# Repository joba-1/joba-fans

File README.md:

# joba-fans — quiet, networked fans for radiators

A small system that puts **PC fans on top of panel radiators** and controls them over WiFi. Its job is
to make a heat pump that cools through wall-hung radiators work properly: a low-mounted radiator hardly
emits any cooling power by free convection, so the heat pump short-cycles. Forced air over the fins
recovers a factor of roughly 3–4 (reasoning and sizing: [fan-mount/docs/requirements.md](fan-mount/docs/requirements.md)).

Four parts, each in its own directory with its own README:

| Part | What it is | Technology |
|---|---|---|
| [`fan-controller/`](fan-controller/) | The board: four PWM fan channels with tach read-back on a socketed ESP32 module | KiCad 10, Python generators |
| [`fan-housing/`](fan-housing/) | A snap-fit 3D-printed case for that board | OpenSCAD |
| [`fan-remote/`](fan-remote/) | The firmware: web remote, MQTT, Home Assistant discovery, soft start | PlatformIO / Arduino-ESP32 |
| [`fan-mount/`](fan-mount/) | 3D-printed mounts that hold 120 mm fans on the radiators | FreeCAD, STL |

## How it fits together

```mermaid
flowchart LR
  subgraph radiator["Radiator"]
    F["PC fans, 120 mm, 4-pin PWM<br/>in <b>fan-mount</b> parts"]
  end
  subgraph box["<b>fan-housing</b> (printed case)"]
    B["<b>fan-controller</b> board<br/>XIAO ESP32-C3<br/>running <b>fan-remote</b>"]
  end
  PSU["12 V supply"] --> B
  B -- "PWM 25 kHz, +12 V<br/>tach back" --> F
  B <-- "WiFi" --> N["Browser (web remote)<br/>MQTT broker + Home Assistant"]
  N -.-> HP["heat-pump / room control<br/>(outside this repo)"]
```

* A **radiator** carries up to ~9 fans in `fan-mount` parts. The fans are standard 120 × 25 mm PC fans.
* Each **controller board** drives four channels; several fans can share a channel (same speed, one tach).
  A 12 V supply feeds the board, which passes 12 V on to the fans.
* The **firmware** gives each board a web page, MQTT topics and a Home Assistant device. Speeds are set
  there — by hand, or by automation (for instance a heat-pump cooling signal in Home Assistant). The
  temperature logic is deliberately *not* part of this repo; the firmware only exposes the fans.
* The **housing** protects the board and brings the barrel jack, USB-C port and four fan cables out.

### The interfaces, and how each was checked

| Interface | Contract | Checked |
|---|---|---|
| firmware ↔ board | FAN1–4: PWM on D1/D3/D7/D6, tach on D2/D4/D10/D5 (GPIO 3/5/20/21 and 4/6/10/7) | The pin table in `fan-remote/src/Fans.cpp` equals the pad nets read out of `fan-controller.kicad_pcb`; the firmware builds for the XIAO ESP32-C3 and C6 and its 22 unit tests pass |
| board ↔ fans | 4-pin PC fan, pinout GND / +12 V / tach / PWM, 25 kHz PWM, 3.3 V logic | Pinout equals the PCB nets of J2–J5; 25 kHz is what the firmware generates. Total current of all fans must stay below the 1.5 A polyfuse |
| board ↔ housing | outer dimensions, connector positions, USB-C end, jack overhang | `fan-housing/board_params.scad` is regenerated from the PCB and is identical; `check_fit.py` passes (latch strain 1.5 %, ≥ 2.2 mm of air above every part, no tab hits a component); the STLs match the OpenSCAD source; the USB-C cut-out sits at the module's USB end (the module's pad rows run along the board's short side, with D6/D7 and the antenna at the other end) |
| fans ↔ mounts | 120 mm fan, 25 mm thick, 105 mm hole pattern | Collar inside 120.6 mm, rest height 2 mm, collar 28 mm; STL sizes match the spreadsheet dimensions (226.6 × 126.6 × 28 mm) |
| firmware ↔ Home Assistant | MQTT discovery, topics `fan-control/<id>/…` | Tested on a bench board with HA (see `fan-remote/docs/test.md`) |
| housing ↔ mounts | none (they only meet through the fans and cables) | — |

Fitting the parts together turned up four things worth knowing; all are written down in the component
READMEs:

1. The fan headers on the board are **unshrouded** — a reversed connector puts 12 V on a tach line
   ([fan-controller](fan-controller/README.md#known-issues)).
2. The PWM lines **float during an ESP reset**, so fans can burst briefly (also fan-controller; a pull-down
   is a candidate for board revision 2).
3. A radiator needs **more fans than a board has channels**, so fans must be chained per channel
   ([fan-mount](fan-mount/README.md#how-it-fits-the-rest-of-the-system)); this has not been tried yet.
4. The firmware has not yet run **on the real board** — only on a bench XIAO with one fan.

## Building it

1. **Board.** Order from the files in [`fan-controller/fab/`](fan-controller/fab/) (a PCB service that does
   assembly; revision 1 went to PCBWay), or regenerate them with `fan-controller/scripts/make_fab.sh`.
   Plug a XIAO ESP32-C3 into the sockets.
2. **Case.** Print the three STLs from [`fan-housing/stl/`](fan-housing/stl/) (PETG, no supports).
3. **Mounts.** Pick the variant for your radiator in [`fan-mount/cad/`](fan-mount/cad/) (the radiator
   sheet geometry is in [`fan-mount/docs/measurements.md`](fan-mount/docs/measurements.md)) and print it in
   PETG. Measure your own radiator first if it differs from the three documented ones.
4. **Firmware.** Register the board and flash it over USB-C, then set WiFi and the MQTT broker in the
   board's setup portal — see [`fan-remote/README.md`](fan-remote/README.md).
5. **Assemble.** Fans into the mounts and onto the radiator, fan cables into the board's headers (check
   that pin 1 = GND), board into the case, 12 V in.

## Repository layout

```text
fan-controller/   KiCad project, generator scripts, fab/ (fabrication package), docs/ (build log)
fan-housing/      OpenSCAD case, STLs, fit check
fan-remote/       PlatformIO firmware, tests, docs/ (spec, user, admin, test)
fan-mount/        FreeCAD models, STLs, scripts, docs/ (requirements, measurements, design notes)
assets/           logo (the fan symbol, also used as favicon) and social-preview image
LICENSE           CC BY-SA 4.0
```

Naming: the directories are named by role. The firmware names itself `fan-control-N` on the network (host
name, MQTT topics, Home Assistant ids) — that is the *device* identity, kept stable for boards that are
already installed, and is not the directory name.

## History and versions

Earlier, the board, the radiator mounts and the firmware lived in separate places. The commit history of
all of them is preserved here, now under the new directory names (messages are left in the language they were
written in, mostly German in the mounts' early history). Commit hashes changed in the merge, so documents
refer to **tags** instead:

| Tag | Meaning |
|---|---|
| `fan-controller-v1` | the board layout that was ordered (schematic and PCB unchanged since) |
| `fan-remote-v1.1.0` | firmware 1.1.0 (the firmware's build info is derived from `fan-remote-v*` tags) |

## Language and licence

Documentation and code comments are in English. Exceptions: the firmware's web page is bilingual
(German/English, by browser language), and the FreeCAD spreadsheets in `fan-mount/cad/` use German parameter
names (glossary in [fan-mount/docs/design-notes.md](fan-mount/docs/design-notes.md)).

[CC BY-SA 4.0](LICENSE). The XIAO symbol and footprints in `fan-controller/libraries/` come from Seeed
Studio's OPL_Kicad_Library, also CC BY-SA 4.0. The firmware pulls in third-party libraries through
PlatformIO under their own licences.

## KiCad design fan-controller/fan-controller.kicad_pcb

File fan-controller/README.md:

# fan-controller — 4-channel PWM fan controller board

A small two-layer board that drives **four 4-pin PC fans** (25 kHz PWM, tach read-back) from a socketed
**Seeed XIAO ESP32-C3**. 12 V in through a barrel jack, 72.9 × 25.0 mm. It is the electronics of the
[joba-fans](../README.md) project; the firmware that runs on it is [`fan-remote`](../fan-remote/), the case
is [`fan-housing`](../fan-housing/), and the fans sit in the [`fan-mount`](../fan-mount/) parts.

**Status:** revision 1 (git tag `fan-controller-v1`) was ordered from PCBWay, 10 boards, fully assembled
except for the XIAO module (the story is in the [build log](docs/build-log.html)). The firmware has so far
been tested on a bench XIAO with one fan, not yet on this board — see
[`fan-remote/docs/test.md`](../fan-remote/docs/test.md).

## Circuit

Per channel the PWM goes through 1 kΩ to the fan, and the tach signal comes back through 330 Ω to the ESP,
with a 10 kΩ pull-up to 3V3. Supply is a barrel jack, an SS34 diode as reverse-polarity protection, a 1.5 A
polyfuse and an AMS1117-5.0 for the ESP (which also provides the 3V3 for the tach pull-ups). The XIAO module
is **socketed** (two 1×7 female headers), not soldered.

### Pin assignment (verified against the PCB)

| Fan | Header | PWM (XIAO pin → GPIO) | Tach (XIAO pin → GPIO) |
|---|---|---|---|
| FAN1 | J2 | D1 → GPIO3 | D2 → GPIO4 |
| FAN2 | J3 | D3 → GPIO5 | D4 → GPIO6 |
| FAN3 | J4 | D7 → GPIO20 | D10 → GPIO10 |
| FAN4 | J5 | D6 → GPIO21 | D5 → GPIO7 |

D0, D8 and D9 are left free — strapping pins of the ESP32-C3 (D8 is suggested for an optional LED, see
[`fan-housing`](../fan-housing/README.md#about-the-led)). The firmware uses exactly this table
(`fan-remote/src/Fans.cpp`); both were checked against the pad nets of the `.kicad_pcb`.

Fan connector pinout (standard PC 4-pin): **1 = GND, 2 = +12 V, 3 = tach, 4 = PWM**.

| Part | Value |
|---|---|
| J1 | DC barrel jack 5.5 × 2.1 mm, 12 V, overhangs the board edge on purpose |
| D1 | SS34, reverse-polarity protection |
| F1 | 1.5 A polyfuse (1812), shared by all four fans and the regulator |
| U2 | AMS1117-5.0 for the XIAO's VBUS pin |
| C1 / C2 | 220 µF electrolytic (leaded, 3.5 mm pitch) / 10 µF 0805 |
| R1–R4 / R5–R8 / R9–R12 | 10 kΩ tach pull-up / 1 kΩ PWM series / 330 Ω tach series |
| J2–J5 | fan headers, 1×4, 2.54 mm |
| U1 | XIAO ESP32-C3 on two 1×7 female headers (the XIAO ESP32-C6 is pin-compatible) |

## Files

| Path | Content |
|---|---|
| `fan-controller.kicad_pro/_sch/_pcb` | the KiCad 10 project (open the `.kicad_pro`) |
| `libraries/` | XIAO symbol and footprints, vendored (see its README for the licence) |
| `scripts/` | Python tools: the schematic is **generated** from `netplan.py` by `generate.py`, the fab files by `make_fab.sh` |
| `fab/` | fabrication package: BOM and pick-and-place for JLCPCB and PCBWay, ordering notes, [fab/README.md](fab/README.md) |
| `docs/build-log.html` | the project page: from the discarded 555 sketch to the order (open in a browser; self-contained) |
| `docs/img/` | renderings of the schematic and the board |

## Working with the project

Regenerate the schematic from the net plan (also checks the exported netlist against the plan — ERC alone
does not find a wire that ends on the wrong pin):

```sh
python3 fan-controller/scripts/generate.py fan-controller/fan-controller.kicad_sch
```

Regenerate the fabrication data (needs `kicad-cli`; gerbers, drill, BOM and CPL in JLCPCB and PCBWay formats,
packed into `fab/fan-controller-fab.zip`):

```sh
fan-controller/scripts/make_fab.sh
```

Checked when this repository was assembled with KiCad 10: ERC 0 violations, DRC 0 violations and 0
unconnected pads; the generator reproduces the schematic (apart from random UUIDs) with all 22 nets matching
the plan; `make_fab.sh` reproduces the tracked BOM and CPL byte for byte.

Ordering: [fab/ORDERING.md](fab/ORDERING.md) (options and decision), [fab/ROTATION-WARNING.md](fab/ROTATION-WARNING.md)
(check D1 and U2 in the assembly preview), [fab/THT-ORDER-LIST.md](fab/THT-ORDER-LIST.md) (parts to source
yourself when the fab does not fit the through-hole parts).

## Known issues

* **The fan headers are unshrouded and unpolarised.** A fan connector plugged in the wrong way round puts
  +12 V on the tach net (header pin 3), which goes through only 330 Ω to an ESP32 GPIO. Check the orientation
  (pin 1 = GND) every time, or fit shrouded/keyed headers when building more boards.
* **The PWM lines have no pull-down.** While the ESP resets (power-up, OTA reboot, watchdog) the pins float and
  a fan's own pull-up asks for full speed — a short burst of up to a few tenths of a second. The firmware
  drives the pins low first thing; fixing it fully would take a 10 kΩ pull-down per line (board revision 2).
* **Total current:** the single 1.5 A polyfuse protects all four fan headers together. Add up the nameplate
  currents of the fans on a board (at most 2 fans per header, 8 per board; see
  [`fan-mount`](../fan-mount/README.md#how-it-fits-the-rest-of-the-system)) and stay below that.
* **Jack and USB-C together:** the XIAO's VBUS pin is fed from the AMS1117; whether the module isolates its
  own USB 5 V from that pin has not been verified here. Flash over USB with the 12 V jack unplugged, or use
  the over-the-air update.

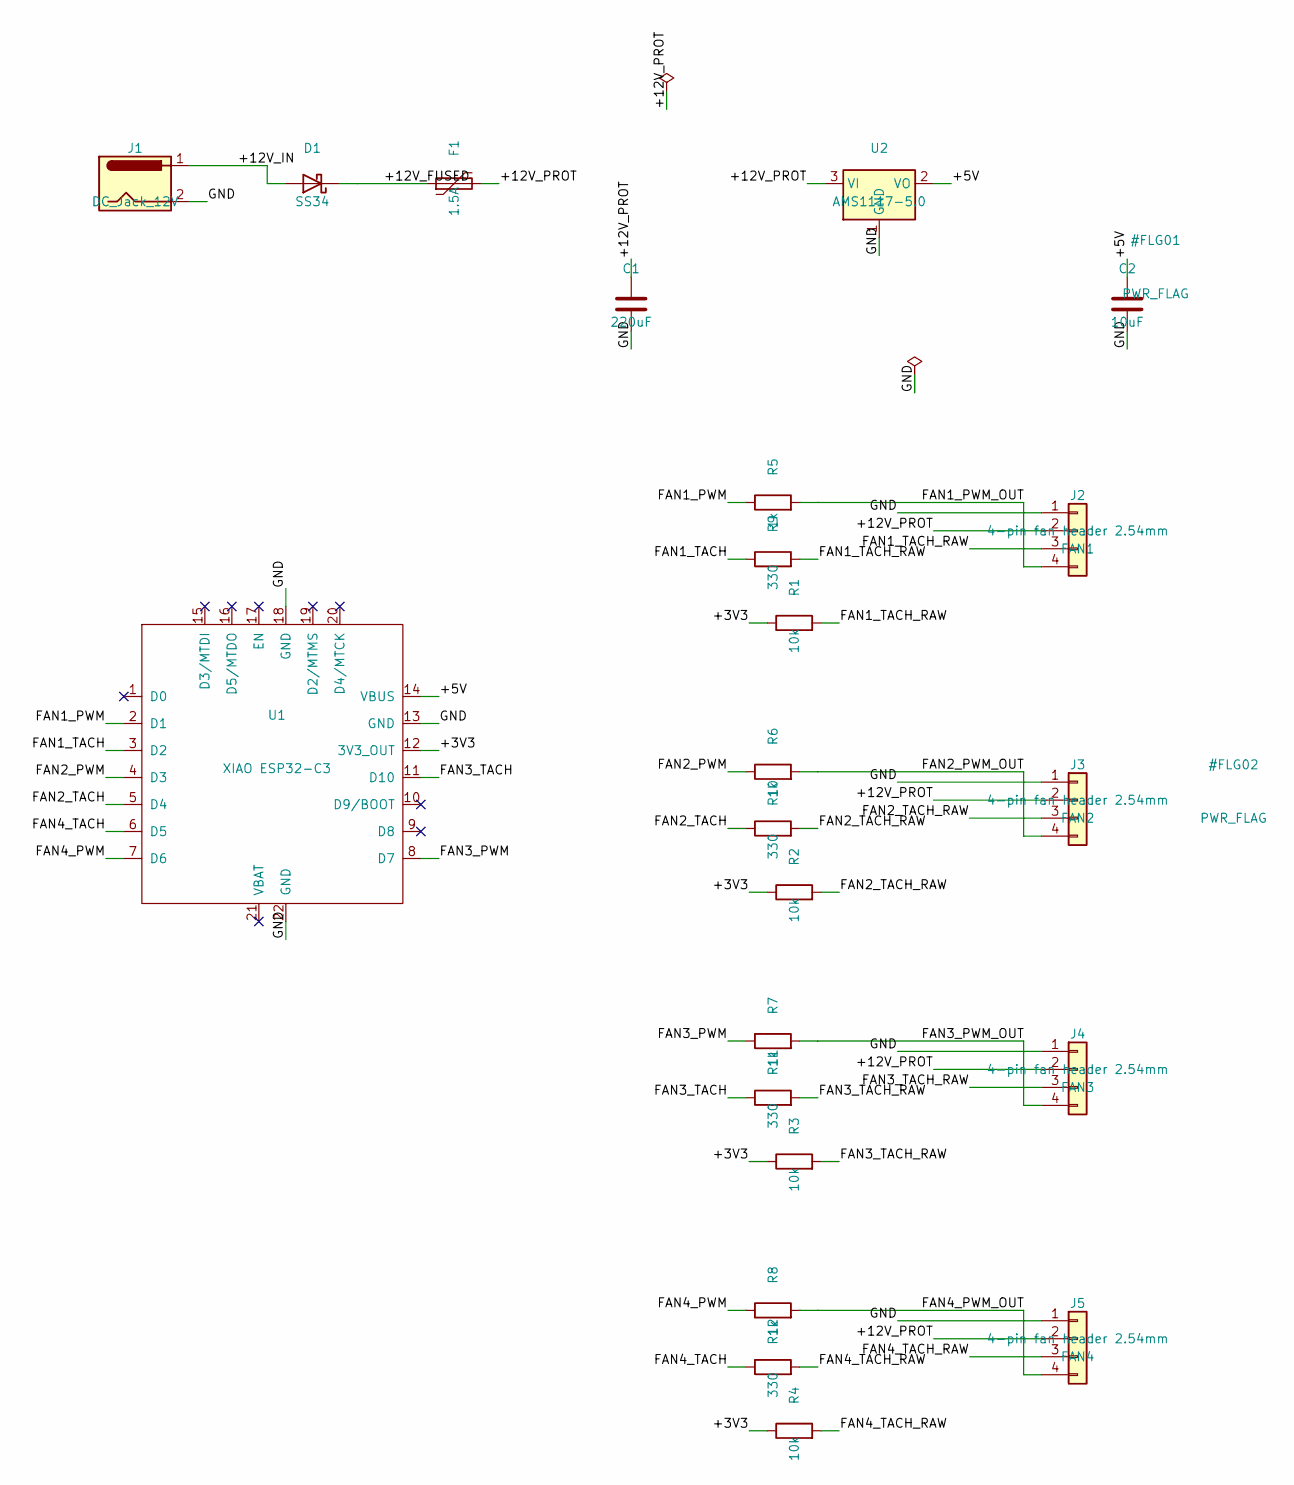
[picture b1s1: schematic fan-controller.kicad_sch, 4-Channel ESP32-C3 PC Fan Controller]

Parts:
C1: 220uF; CP_Radial_D8.0mm_P3.50mm
C2: 10uF; C_0805_2012Metric
D1: SS34; D_SMA
F1: 1.5A; Fuse_1812_4532Metric
J1: DC_Jack_12V; BarrelJack_CUI_PJ-102AH_Horizontal
J2: FAN1; PinHeader_1x04_P2.54mm_Vertical
J3: FAN2; PinHeader_1x04_P2.54mm_Vertical
J4: FAN3; PinHeader_1x04_P2.54mm_Vertical
J5: FAN4; PinHeader_1x04_P2.54mm_Vertical
R1, R2, R3, R4: 10k; R_0603_1608Metric
R5, R6, R7, R8: 1k; R_0603_1608Metric
R9, R10, R11, R12: 330; R_0603_1608Metric
U1: XIAO ESP32-C3; XIAO-ESP32-C3-DIP
U2: AMS1117-5.0; SOT-223-3_TabPin2

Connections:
/+3V3: R1.1, R2.1, R3.1, R4.1, U1.12 (3V3_OUT)
/+5V: C2.1, U1.14 (VBUS), U2.2 (VO)
/+12V_FUSED: D1.1 (K), F1.1
/+12V_IN: D1.2 (A), J1.1
/+12V_PROT: C1.1, F1.2, J2.2, J3.2, J4.2, J5.2, U2.3 (VI)
/FAN1_PWM: R5.1, U1.2 (D1)
/FAN1_PWM_OUT: J2.4, R5.2
/FAN1_TACH: R9.1, U1.3 (D2)
/FAN1_TACH_RAW: J2.3, R1.2, R9.2
/FAN2_PWM: R6.1, U1.4 (D3)
/FAN2_PWM_OUT: J3.4, R6.2
/FAN2_TACH: R10.1, U1.5 (D4)
/FAN2_TACH_RAW: J3.3, R2.2, R10.2
/FAN3_PWM: R7.1, U1.8 (D7)
/FAN3_PWM_OUT: J4.4, R7.2
/FAN3_TACH: R11.1, U1.11 (D10)
/FAN3_TACH_RAW: J4.3, R3.2, R11.2
/FAN4_PWM: R8.1, U1.7 (D6)
/FAN4_PWM_OUT: J5.4, R8.2
/FAN4_TACH: R12.1, U1.6 (D5)
/FAN4_TACH_RAW: J5.3, R4.2, R12.2
/GND: C1.2, C2.2, J1.2, J2.1, J3.1, J4.1, J5.1, U1.13 (GND), U1.18 (GND), U1.22 (GND), U2.1 (GND)

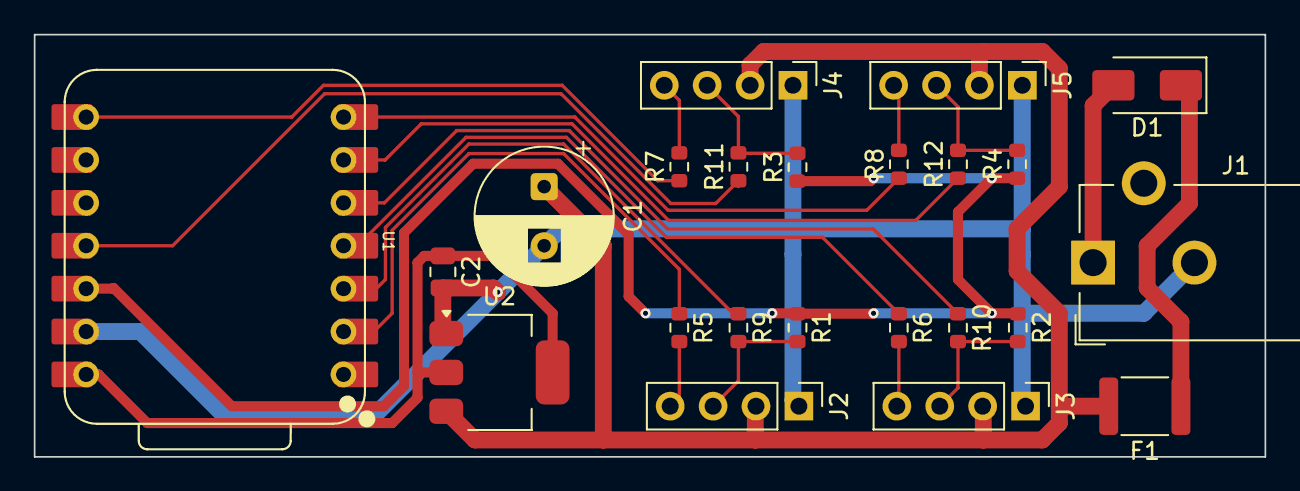
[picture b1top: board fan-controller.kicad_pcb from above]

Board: 2 copper layers, 72.9 x 25.0 mm, 23 parts (0 on the bottom side), 22 nets.

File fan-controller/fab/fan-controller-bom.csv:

Comment,Designator,Footprint,LCSC Part #
220uF,C1,Capacitor_THT:CP_Radial_D8.0mm_P3.50mm,
10uF,C2,Capacitor_SMD:C_0805_2012Metric,
SS34,D1,Diode_SMD:D_SMA,
1.5A,F1,Fuse:Fuse_1812_4532Metric,
DC barrel jack 5.5x2.1mm,J1,Connector_BarrelJack:BarrelJack_CUI_PJ-102AH_Horizontal,
4-pin PC fan header,"J2,J3,J4,J5",Connector_PinHeader_2.54mm:PinHeader_1x04_P2.54mm_Vertical,
10k,"R1,R2,R3,R4",Resistor_SMD:R_0603_1608Metric,
1k,"R5,R6,R7,R8",Resistor_SMD:R_0603_1608Metric,
330,"R9,R10,R11,R12",Resistor_SMD:R_0603_1608Metric,
1x7 female header 2.54mm - 2 Stk pro Platine - Modul wird spaeter gesteckt,U1,Seeed_Studio_XIAO_Series:XIAO-ESP32-C3-DIP,
AMS1117-5.0,U2,Package_TO_SOT_SMD:SOT-223-3_TabPin2,
